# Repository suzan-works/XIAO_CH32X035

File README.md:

# サポートページ：CH32X035搭載XIAOピン互換ボード Support page for CH32X035 XIAO-Compatible Board #XIAO_CH32X035
WCH CH32X035を搭載した小型のマイコンボードです。
Arduino IDEからプログラム可能で、USB PDシンクとして動作できます。

Tiny microcontroller board equipped with WCH CH32X035. 
It can be programmed from the Arduino IDE and functions as a USB PD sink.  

## CH32X035搭載XIAOピン互換ボード CH32X035 XIAO-Compatible Board
WCH CH32X035搭載のUSB PD対応マイコンボードです。  

[回路図PDF](hardware/CH32X035_XIAO-Compatible_Board/CH32X035_XIAO-Compatible_Board.pdf)  
[回路図をブラウザで見る](https://kicanvas.org/?github=https%3A%2F%2Fgithub.com%2Fsuzan-works%2FXIAO_CH32X035%2Fblob%2Fmain%2Fhardware%2FCH32X035_XIAO-Compatible_Board%2FCH32X035_XIAO-Compatible_Board.kicad_sch)  
[基板データをブラウザで見る](https://kicanvas.org/?github=https%3A%2F%2Fgithub.com%2Fsuzan-works%2FXIAO_CH32X035%2Fblob%2Fmain%2Fhardware%2FCH32X035_XIAO-Compatible_Board%2FCH32X035_XIAO-Compatible_Board.kicad_pcb)  
  
## SWD変換基板 SWD Converter Board
デバッガWCH-LinkEとマイコンボード上のコネクタ(1.27mm 10P)を接続するための変換基板です。  

[回路図PDF](hardware/SWD_Converter_Board/SWD_Converter_Board.pdf)  
[回路図をブラウザで見る](https://kicanvas.org/?github=https%3A%2F%2Fgithub.com%2Fsuzan-works%2FXIAO_CH32X035%2Fblob%2Fmain%2Fhardware%2FSWD_Converter_Board%2FSWD_Converter_Board.kicad_sch)  
[基板データをブラウザで見る](https://kicanvas.org/?github=https%3A%2F%2Fgithub.com%2Fsuzan-works%2FXIAO_CH32X035%2Fblob%2Fmain%2Fhardware%2FSWD_Converter_Board%2FSWD_Converter_Board.kicad_pcb)  
  
## VBUSスイッチアドオンボード VBUS Switch Add-on Board
マイコンボードからVBUS出力のオンオフを切り替えられるアドオンボードです。

[回路図PDF](hardware/VBUS_Switch_Addon_Board/VBUS_Switch_Addon_Board.pdf)  
[回路図をブラウザで見る](https://kicanvas.org/?github=https%3A%2F%2Fgithub.com%2Fsuzan-works%2FXIAO_CH32X035%2Fblob%2Fmain%2Fhardware%2FVBUS_Switch_Addon_Board%2FVBUS_Switch_Addon_Board.kicad_sch)  
[基板データをブラウザで見る](https://kicanvas.org/?github=https%3A%2F%2Fgithub.com%2Fsuzan-works%2FXIAO_CH32X035%2Fblob%2Fmain%2Fhardware%2FVBUS_Switch_Addon_Board%2FVBUS_Switch_Addon_Board.kicad_pcb)  
  
## 導入手順
### Arduino IDE
WCH arduino_core_ch32をインストールすることで、Arduino IDEで開発ができます。  
https://github.com/openwch/arduino_core_ch32  
ボード設定でCH32X035を選択してください。
### 初期ファームウェア
[PreInstalledFirmware.ino](software/examples/PreInstalledFirmware/PreInstalledFirmware.ino) : 5秒ごとにUSB PDの電圧を切り替えます。テスター等でVBUS-GND間の電圧をご確認ください。

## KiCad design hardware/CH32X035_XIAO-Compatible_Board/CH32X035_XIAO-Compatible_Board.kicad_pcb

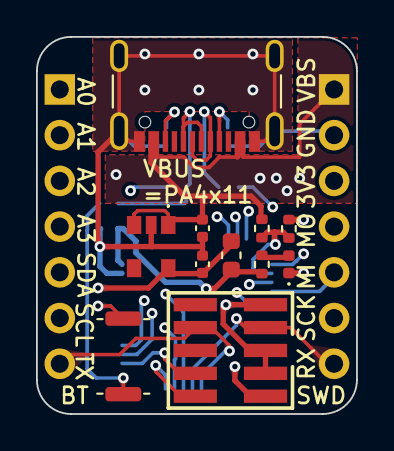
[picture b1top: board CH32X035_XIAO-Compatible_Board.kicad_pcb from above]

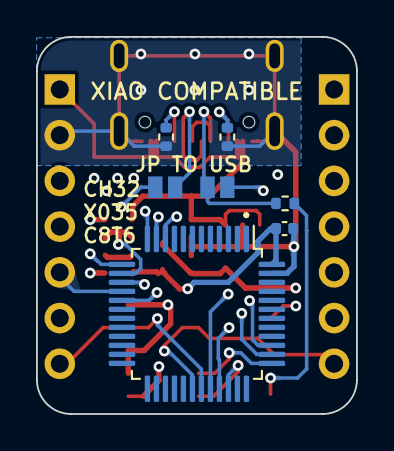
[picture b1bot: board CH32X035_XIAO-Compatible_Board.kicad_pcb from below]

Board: 4 copper layers, 17.8 x 21.0 mm, 20 parts (9 on the bottom side), 24 nets.

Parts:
C1, C2: C_Small; C_0402_1005Metric
C3: 0.1uF; C_0402_1005Metric
D1: LED; LED_0402_1005Metric
F1: Polyfuse_Small; Fuse_0603_1608Metric
IC1: TCR1HF33B; TCR1HF33BLMCT
J1: GCT USB4105; USB_C_Receptacle_GCT_USB4105-xx-A_16P_TopMnt_Horizontal
J2, J3: Conn_01x07; PinHeader_1x07_P2.54mm_Vertical
J4: Conn_02x05_Odd_Even; PinHeader_2x05_P1.27mm_Vertical_SMD
JP1, JP2: SolderJumper_2_Open; SolderJumper-2_P1.3mm_Open_Pad0.8x1.2mm
R1, R2: 5.1k; R_0402_1005Metric
R3: 4.7k; R_0402_1005Metric
R4, R5, R6: R_Small; R_0402_1005Metric
SW1: SW_Push; SW_Push_SPST_NO_Alps_SKRK
U3: CH32X035C8T6; LQFP-48_7x7mm_P0.5mm

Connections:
+3.3V: C3.1, F1.2, J3.3, R4.1, SW1.2, U3.48 (VDD)
+3.3VA: C2.1, F1.1, IC1.5 (VOUT), J4.1
/CC1: J1.A5 (CC1), R2.1, U3.38 (PC14/CC1)
/CC2: J1.B5 (CC2), R1.1, U3.39 (PC15/CC2)
/DIVIDE_VOLT: R5.2, R6.1, U3.14 (PA4/CS)
/MISO: J3.5, U3.16 (PA6/MISO)
/MOSI: J3.4, U3.17 (PA7/MOSI)
/PA0: J2.1, U3.10 (PA0)
/PA1: J2.2, U3.11 (PA1)
/PA2: J2.3, U3.12 (PA2)
/PA3: J2.4, U3.13 (PA3)
/RX: J3.7, J4.7, U3.31 (PB11/RX)
/SCK: J3.6, U3.15 (PA5/SCK)
/SCL: J2.6, JP1.2 (B), U3.32 (PC16/UDM)
/SDA: J2.5, JP2.2 (B), U3.33 (PC17/UDP)
/SWCLK: J4.4, U3.37 (PC19/DCK)
/SWDIO: J4.2, U3.34 (PC18/DIO)
/TX: J2.7, J4.8, U3.30 (PB10/TX)
/UDM: J1.A7 (D-), J1.B7 (D-), JP1.1 (A)
/UDP: J1.A6 (D+), J1.B6 (D+), JP2.1 (A), R3.2
GND: C1.2, C2.2, C3.2, D1.1 (K), IC1.2 (GND), J1.A1 (GND), J1.A12 (GND), J1.B1 (GND), J1.B12 (GND), J1.S1 (SHIELD), J3.2, J4.3, J4.5, J4.9, R1.2, R2.2, R6.2, U3.47 (GND)
unnamed: D1.2 (A), R4.2
unnamed: R3.1, SW1.1
VBUS: C1.1, IC1.1 (VIN), IC1.3 (CONTROL), J1.A4 (VBUS), J1.A9 (VBUS), J1.B4 (VBUS), J1.B9 (VBUS), J3.1, R5.1

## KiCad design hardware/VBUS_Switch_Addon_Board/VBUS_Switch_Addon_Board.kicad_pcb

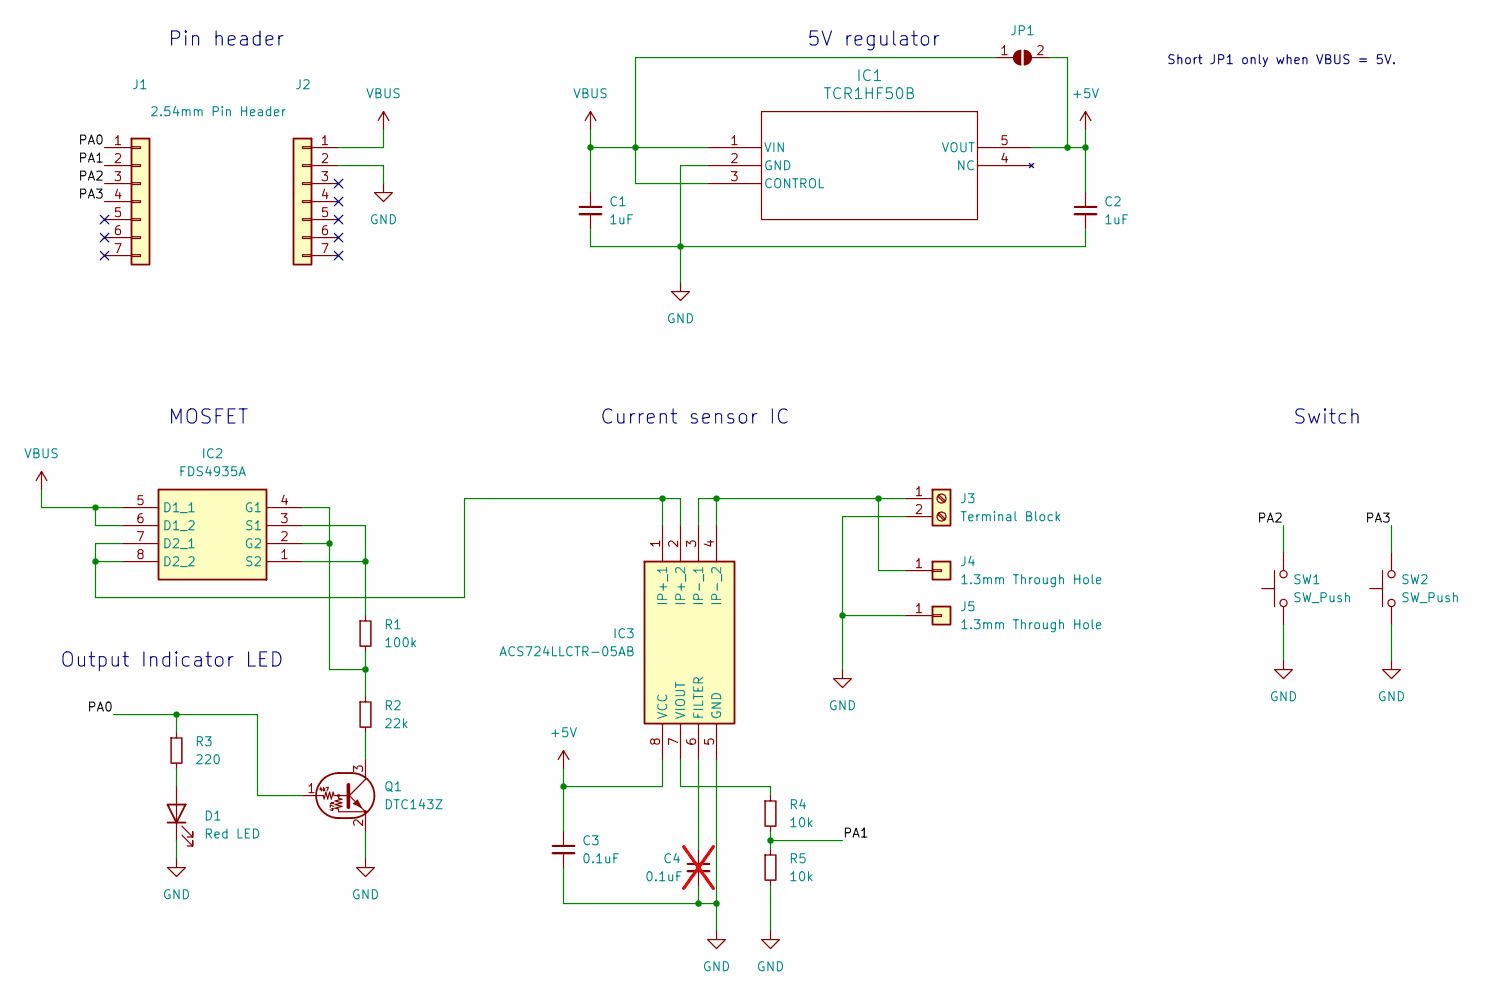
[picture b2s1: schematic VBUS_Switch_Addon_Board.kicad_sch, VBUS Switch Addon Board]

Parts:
C1, C2: 1uF; C_0402_1005Metric
C3: 0.1uF; C_0402_1005Metric
C4: 0.1uF; C_0402_1005Metric; not fitted
D1: Red LED; LED_0402_1005Metric
IC1: TCR1HF50B
IC2: FDS4935A; Manufacturer_Part_Number FDS4935A
IC3: ACS724LLCTR-05AB; Manufacturer_Part_Number ACS724LLCTR-05AB-T
J1: 2.54mm Pin Header; PinHeader_1x07_P2.54mm_Vertical
J2: Conn_01x07; PinHeader_1x07_P2.54mm_Vertical
J3: Terminal Block; TerminalBlock_TE_282834-2_1x02_P2.54mm_Horizontal
J4, J5: 1.3mm Through Hole; Pin_D1.3mm_L11.0mm
JP1: SolderJumper_2_Open; SolderJumper-2_P1.3mm_Open_Pad0.8x1.2mm
Q1: DTC143Z; SOT-323_SC-70
R1: 100k; R_0402_1005Metric
R2: 22k; R_0402_1005Metric
R3: 220; R_0402_1005Metric
R4, R5: 10k; R_0402_1005Metric
SW1, SW2: SW_Push; SW_Push_SPST_NO_Alps_SKRK

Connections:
+5V: C2.1, C3.1, IC1.5 (VOUT), IC3.8 (VCC), JP1.2 (B)
/PA0: J1.1, Q1.1 (B), R3.1
/PA1: J1.2, R4.2, R5.1
/PA2: J1.3, SW1.2
/PA3: J1.4, SW2.2
GND: C1.2, C2.2, C3.2, C4.2, D1.1 (K), IC1.2 (GND), IC3.5 (GND), J2.2, J3.2, J5.1, Q1.2 (E), R5.2, SW1.1, SW2.1
unnamed: D1.2 (A), R3.2
unnamed: IC2.7 (D2_1), IC2.8 (D2_2), IC3.1 (IP+_1), IC3.2 (IP+_2)
unnamed: IC2.2 (G2), IC2.4 (G1), R1.2, R2.1
unnamed: IC2.1 (S2), IC2.3 (S1), R1.1
unnamed: C4.1, IC3.6 (FILTER)
unnamed: IC3.3 (IP-_1), IC3.4 (IP-_2), J3.1, J4.1
unnamed: IC3.7 (VIOUT), R4.1
unnamed: Q1.3 (C), R2.2
VBUS: C1.1, IC1.1 (VIN), IC1.3 (CONTROL), IC2.5 (D1_1), IC2.6 (D1_2), J2.1, JP1.1 (A)

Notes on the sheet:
Output Indicator LED
Switch
5V regulator
Current sensor IC
MOSFET
Pin header
Short JP1 only when VBUS = 5V.

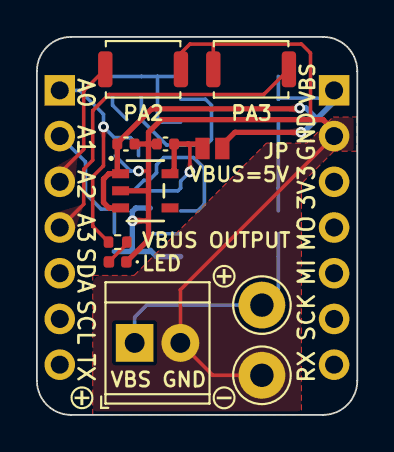
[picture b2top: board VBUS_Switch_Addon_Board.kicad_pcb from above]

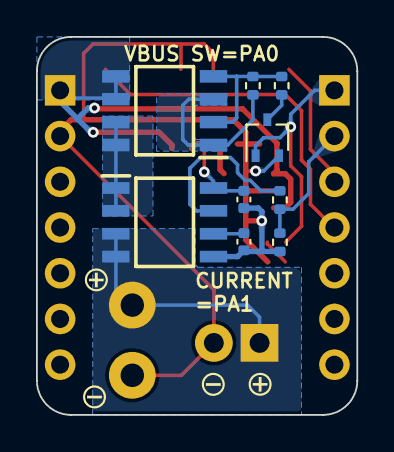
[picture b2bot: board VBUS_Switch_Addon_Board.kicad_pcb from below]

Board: 2 copper layers, 17.8 x 21.0 mm, 22 parts (11 on the bottom side), 15 nets.

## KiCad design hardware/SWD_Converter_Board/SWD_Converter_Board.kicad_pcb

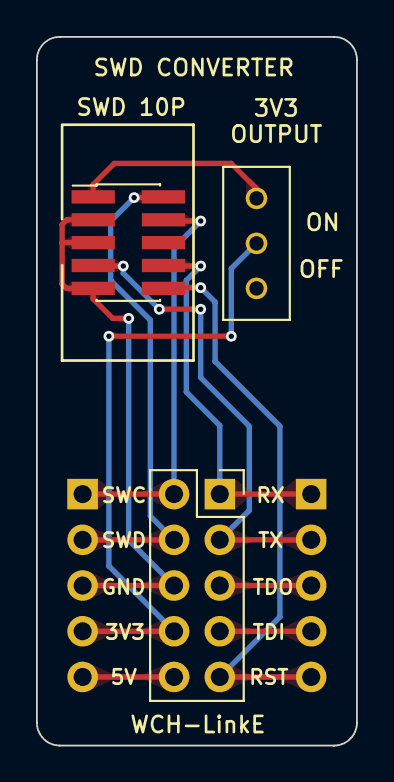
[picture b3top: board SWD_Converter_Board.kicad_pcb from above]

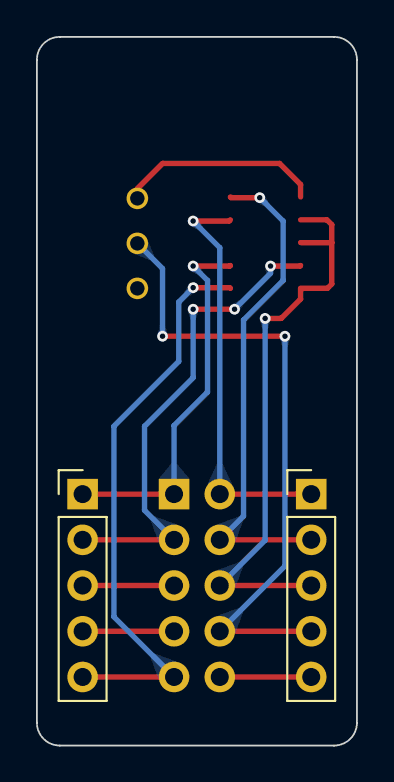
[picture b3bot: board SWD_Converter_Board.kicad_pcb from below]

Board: 2 copper layers, 17.8 x 39.4 mm, 5 parts (2 on the bottom side), 11 nets.

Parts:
J1: Conn_02x05_Odd_Even; PinSocket_2x05_P2.54mm_Vertical
J2: Conn_02x05_Odd_Even; PinHeader_2x05_P1.27mm_Vertical_SMD
J3, J4: Conn_01x05; PinHeader_1x05_P2.54mm_Vertical
SW1: SW_SPDT; SS-12D00G3

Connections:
/3V3: J1.8, J4.4, SW1.2 (B)
/3V3OUT: J2.1, SW1.1 (A)
/5V: J1.10, J4.5
/GND: J1.6, J2.3, J2.5, J2.9, J4.3
/RST: J1.9, J2.10, J3.5
/RX: J1.1, J2.8, J3.1
/SWCLK: J1.2, J2.4, J4.1
/SWDIO: J1.4, J2.2, J4.2
/TDI: J1.7, J3.4
/TDO: J1.5, J3.3
/TX: J1.3, J2.7, J3.2

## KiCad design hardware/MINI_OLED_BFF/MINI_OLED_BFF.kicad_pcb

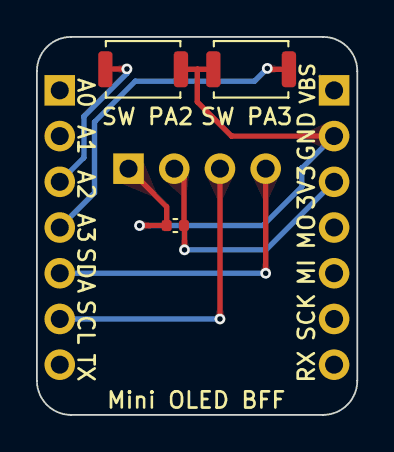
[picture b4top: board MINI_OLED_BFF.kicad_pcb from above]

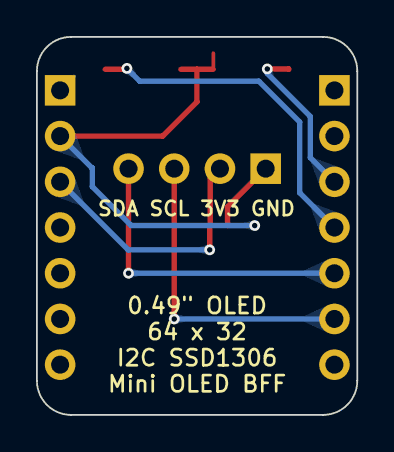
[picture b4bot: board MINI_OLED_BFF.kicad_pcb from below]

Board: 2 copper layers, 17.8 x 21.0 mm, 6 parts (2 on the bottom side), 6 nets.

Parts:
C1: C_Small; C_0402_1005Metric
J1, J2: Conn_01x07; PinHeader_1x07_P2.54mm_Vertical
J3: Conn_01x04; PinHeader_1x04_P2.54mm_Vertical
SW1, SW2: SW_Push; SW_Push_SPST_NO_Alps_SKRK

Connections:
+3.3V: C1.1, J2.3, J3.2
/PA2: J1.3, SW1.2
/PA3: J1.4, SW2.2
/SCL: J1.6, J3.3
/SDA: J1.5, J3.4
GND: C1.2, J2.2, J3.1, SW1.1, SW2.1

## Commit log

2024-05-09 回路図と外観写真を追加
2024-06-24 フォルダ構成変更
2024-06-24 回路図と写真を追加
2024-06-24 回路図を追加
2024-06-24 YouTubeリンクを追記
2024-06-27 KiCadファイル追加
2024-06-27 KiCanvas表示を追加
2024-06-27 READMEにKiCanvas表示を追加
2024-07-13 examplesを追加
2024-07-13 READMEを追記
2024-07-14 READMEにデモ動画リンクを追加
2024-09-02 サポートページ用の回路図・基板設計データの変更
2024-09-16 サポートページとして構成変更
2024-09-17 サポートページの拡充
2024-09-17 初期ファームウェア追加
2024-09-18 初期ファームウェアにコメント追記
2024-09-18 README追記
